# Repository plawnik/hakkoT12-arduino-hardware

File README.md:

# hakkoT12-arduino-hardware
Hardware part of simple HAKKO T12 soldering station based on this firmware https://github.com/sfrwmaker/hakko_t12

Drawed in Cadsoft Eagle 7.7.0

Single sided pcb, only THT parts.
Arduino pro mini + encoder + lcd 1602 hd44780 on i2c or lcd 0802 hd44780 on parallel 4 bit mode.

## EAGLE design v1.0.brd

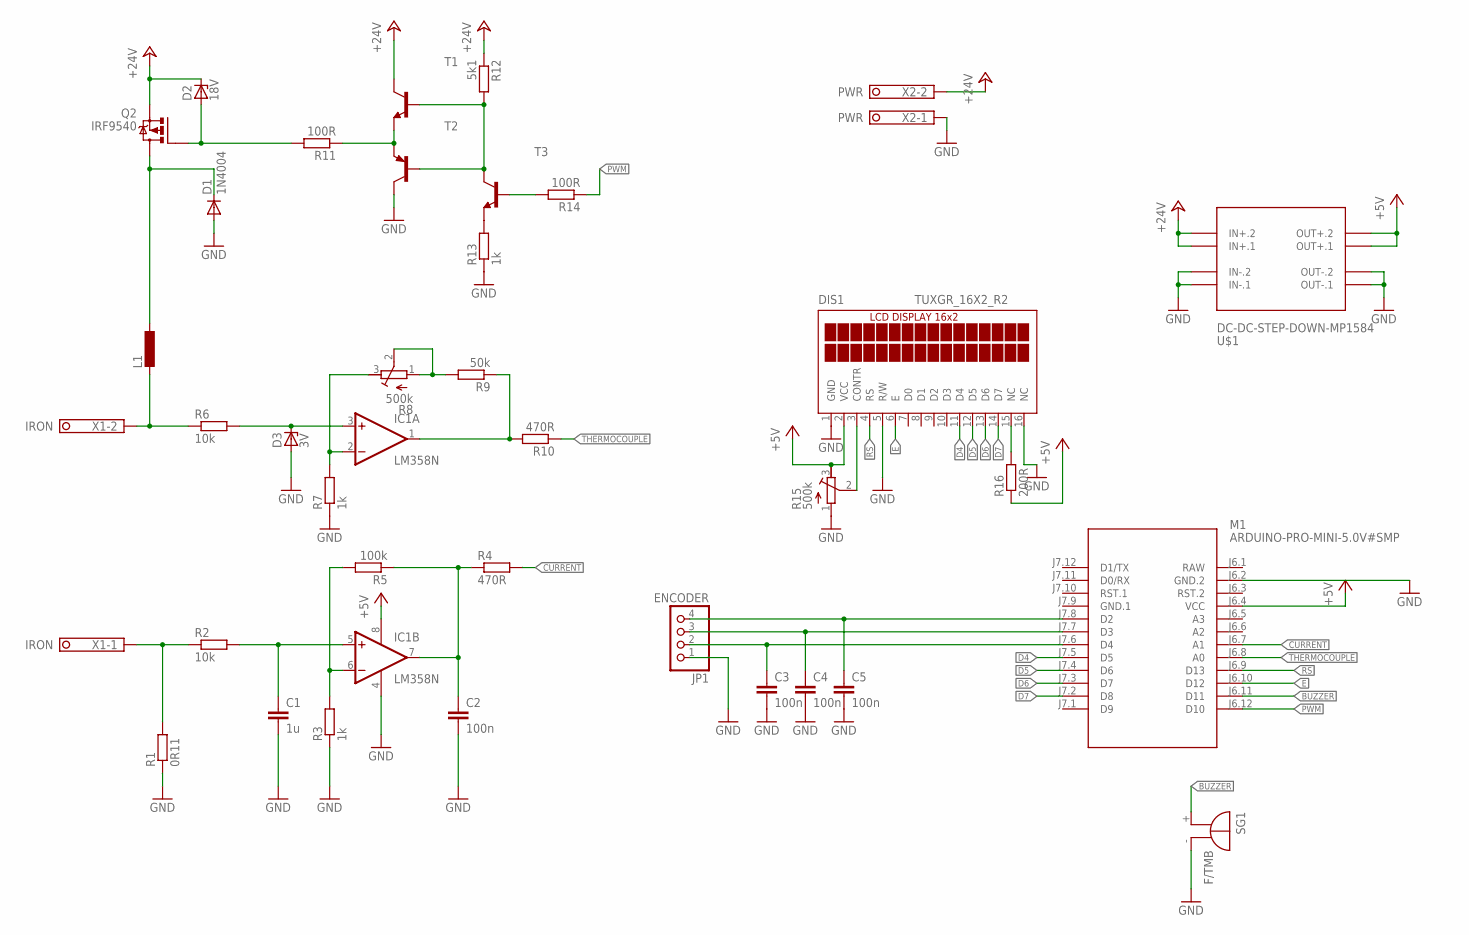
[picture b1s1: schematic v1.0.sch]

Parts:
C1: 1u; C025-025X050
C2, C3, C4, C5: 100n; C025-025X050
D1: 1N4004; DO41-10
D2: 18V; DO35Z10
D3: 3V; DO35Z10
DIS1: TUXGR_16X2_R2
IC1: LM358N; DIL08
JP1: ENCODER; 1X04
L1: L-EULAL02; LAL02
M1: ARDUINO-PRO-MINI-5.0V#SMP; ARDUINO-PRO-MINI#SMP
Q2: IRF9540; TO220BV
R1: 0R11; 0617/22
R2, R6: 10k; 0204/7
R3, R7, R13: 1k; 0204/7
R4, R10: 470R; 0204/7
R5: 100k; 0204/7
R8, R15: 500k; RTRIM3296Y
R9: 50k; 0204/7
R11, R14: 100R; 0204/7
R12: 5k1; 0204/7
R16: 200R; 0204/7
SG1: F/TMB
T1, T3: BC547-NPN-TO92-CBE; TO92-CBE
T2: BC557A-PNP-TO92-EBC; TO92-EBC
U$1: DC-DC-STEP-DOWN-MP1584
X1: IRON; 1751248
X2: PWR; 1751248

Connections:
+5V: DIS1.2 (VCC), IC1.8 (V+), M1.J6.4 (VCC), R15.3 (E), R16.1, U$1.OUT+.1, U$1.OUT+.2
+24V: D2.C, Q2.S, R12.1, T1.C, U$1.IN+.1, U$1.IN+.2, X2.2
BUZZER: M1.J6.11 (D11), SG1.+
CURRENT: M1.J6.7 (A1), R4.2
D4: DIS1.11 (D4), M1.J7.5 (D5)
D5: DIS1.12 (D5), M1.J7.4 (D6)
D6: DIS1.13 (D6), M1.J7.3 (D7)
D7: DIS1.14 (D7), M1.J7.2 (D8)
E: DIS1.6 (E), M1.J6.10 (D12)
GND: C1.2, C2.2, C3.2, C4.2, C5.2, D1.A, D3.A, DIS1.1 (GND), DIS1.5 (R/W), DIS1.16 (NC), IC1.4 (V-), JP1.1, M1.J6.2 (GND.2), R1.1, R3.1, R7.1, R13.1, R15.1 (A), SG1.-, T2.C, U$1.IN-.1, U$1.IN-.2, U$1.OUT-.1, U$1.OUT-.2, X2.1
GND.1: M1.J7.9 (GND.1)
HEATER+: L1.2, R6.1, X1.2
HEATER-: R1.2, R2.1, X1.1
unnamed: C1.1, IC1.5 (+IN), R2.2
unnamed: IC1.6 (-IN), R3.2, R5.2
unnamed: C2.1, IC1.7 (OUT), R4.1, R5.1
unnamed: D3.C, IC1.3 (+IN), R6.2
unnamed: IC1.2 (-IN), R7.2, R8.3 (E)
unnamed: R8.1 (A), R8.2 (S), R9.2
unnamed: IC1.1 (OUT), R9.1, R10.2
unnamed: D1.C, L1.1, Q2.D
unnamed: R12.2, T1.B, T2.B, T3.C
unnamed: D2.A, Q2.G, R11.2
unnamed: R11.1, T1.E, T2.E
unnamed: R13.2, T3.E
unnamed: R14.2, T3.B
unnamed: C5.1, JP1.4, M1.J7.8 (D2)
unnamed: C4.1, JP1.3, M1.J7.7 (D3)
unnamed: C3.1, JP1.2, M1.J7.6 (D4)
unnamed: DIS1.3 (CONTR), R15.2 (S)
unnamed: DIS1.15 (NC), R16.2
PWM: M1.J6.12 (D10), R14.1
RAW: M1.J6.1 (RAW)
RS: DIS1.4 (RS), M1.J6.9 (D13)
THERMOCOUPLE: M1.J6.8 (A0), R10.1

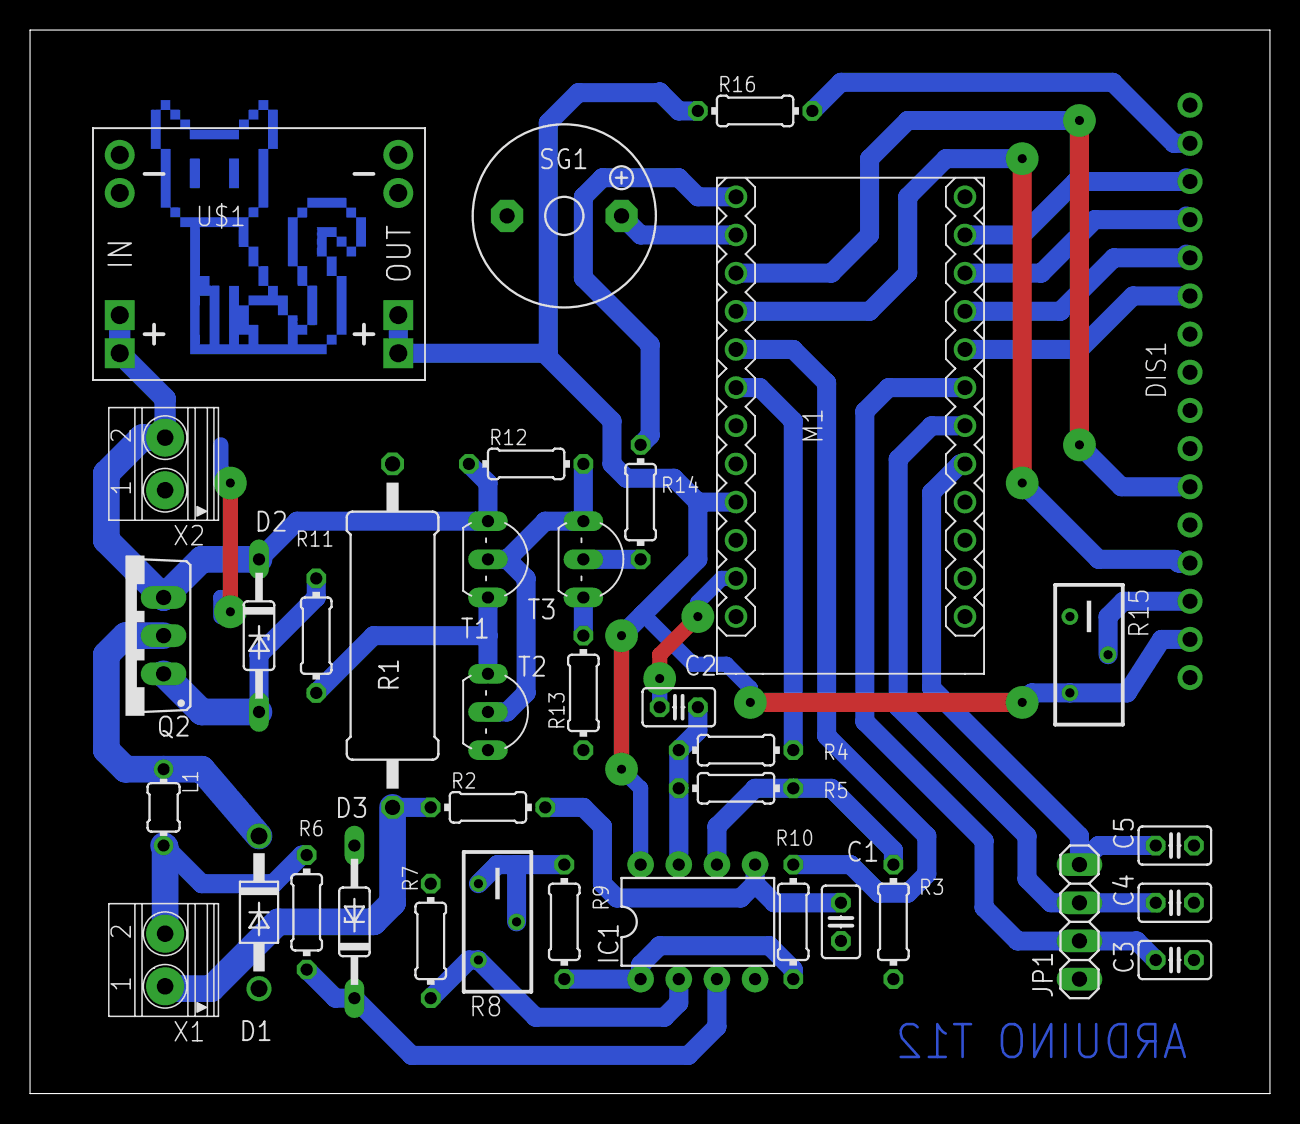
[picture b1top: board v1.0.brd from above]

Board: 2 copper layers, 82.5 x 70.8 mm, 37 parts (0 on the bottom side), 33 nets.

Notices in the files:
parts and their libraries:
diy-modules: Released under the Creative Commons Attribution 4.0 International License: http://creativecommons.org/licenses/by/4.0
